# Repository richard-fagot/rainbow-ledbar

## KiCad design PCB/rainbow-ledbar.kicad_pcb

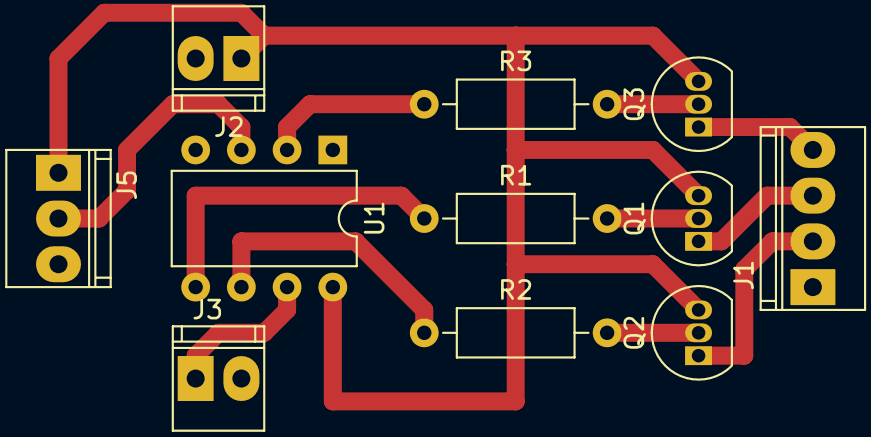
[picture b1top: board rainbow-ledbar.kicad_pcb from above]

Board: 2 copper layers, 11 parts (0 on the bottom side), 13 nets.

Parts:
J1: Leds; Gotronic_S004
J2: Alimentation; Gotronic_S002
J3: Pushbutton; Gotronic_S002
J5: Potentiomètre; Gotronic_S003
Q1, Q2, Q3: PN2222A; TO-92_Inline
R1, R2, R3: 1k; R_Axial_DIN0207_L6.3mm_D2.5mm_P10.16mm_Horizontal
U1: ATtiny85-20PU; DIP-8_W7.62mm

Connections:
B: R1.1, U1.5
G: R2.1, U1.6
GNDREF: J1.1, J2.2, J3.2, J5.3, U1.4
unnamed: J1.2, Q2.1
unnamed: J1.3, Q1.1
unnamed: J1.4, Q3.1
unnamed: Q1.2, R1.2
unnamed: Q2.2, R2.2
unnamed: Q3.2, R3.2
Potentiomètre: J5.2, U1.3
PushButton: J3.1, U1.7
R: R3.1, U1.2
VCC: J2.1, J5.1, Q1.3, Q2.3, Q3.3, U1.8

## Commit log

2018-11-09 Init
2020-11-14 Kicad files
2020-11-25 Actualisation du script
2021-11-28 Fix bad potar pin ref number
